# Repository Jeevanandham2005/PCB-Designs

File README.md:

View this project on [CADLAB.io](https://cadlab.io/project/29114). 

# PCB-Designs

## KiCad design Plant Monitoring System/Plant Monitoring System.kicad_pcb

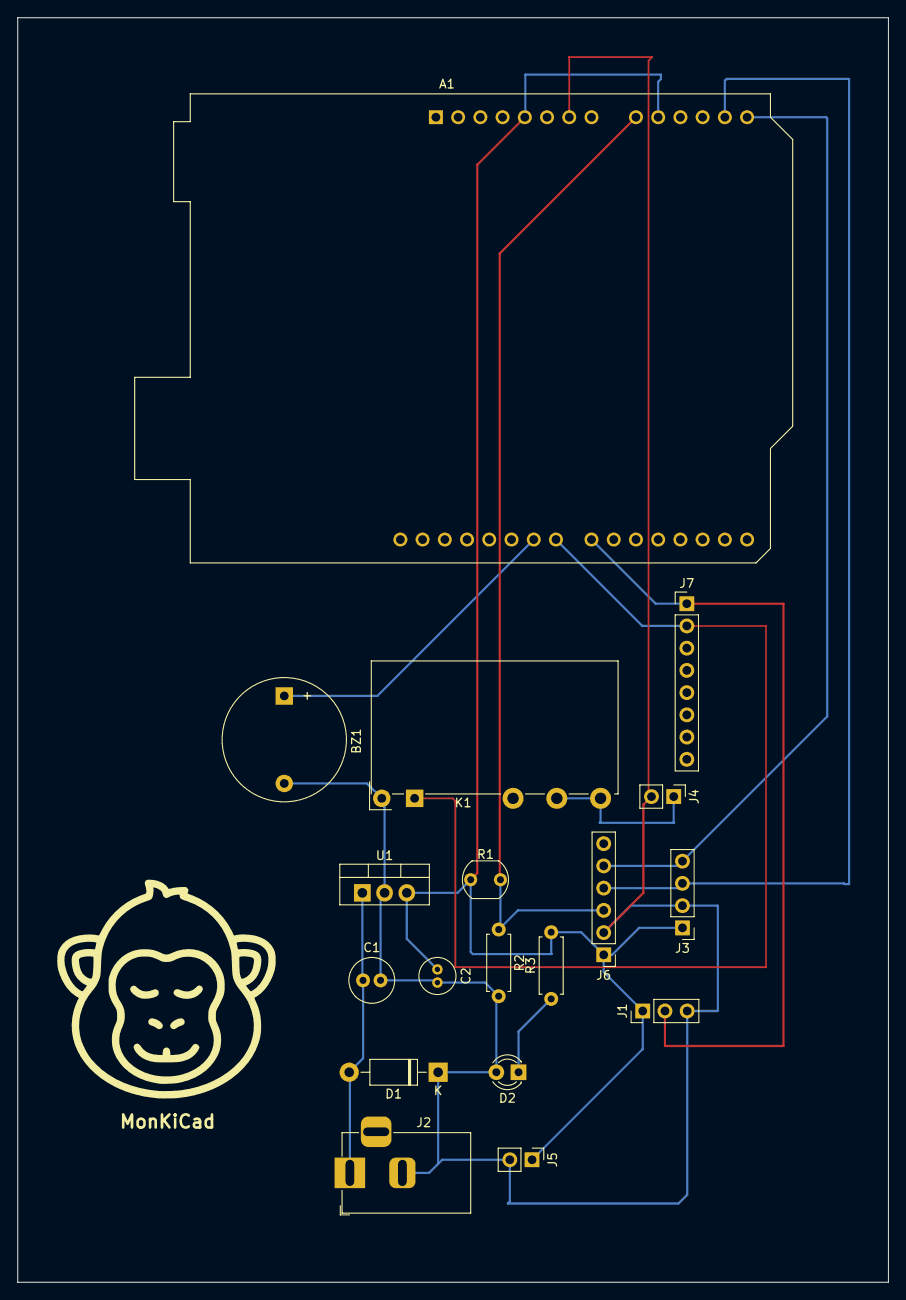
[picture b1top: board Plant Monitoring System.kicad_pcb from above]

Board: 2 copper layers, 99.5 x 144.5 mm, 19 parts (0 on the bottom side), 11 nets.

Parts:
A1: Arduino_UNO_R2
BZ1: Buzzer; Buzzer_D14mm_H7mm_P10mm
C1: 100uF; C_Radial_D5.0mm_H11.0mm_P2.00mm
C2: 10uF; C_Radial_D4.0mm_H5.0mm_P1.50mm
D1: 1N4007; D_DO-41_SOD81_P10.16mm_Horizontal
D2: LED; LED_D3.0mm
J1: DHT11_Connector; PinHeader_1x03_P2.54mm_Vertical
J2: Barrel_Jack; BarrelJack_Horizontal
J3: Soil_Sensor_Connector; PinHeader_1x04_P2.54mm_Vertical
J4, J5: Conn_01x02_Pin; PinHeader_1x02_P2.54mm_Vertical
J6: Conn_01x06_Pin; PinHeader_1x06_P2.54mm_Vertical
J7: Conn_01x08_Pin; PinHeader_1x08_P2.54mm_Vertical
K1: Relay_SPDT; Relay_SPDT_Finder_34.51_Horizontal
Logo: LOGO; monkicadlogo
R1: LDR07; R_LDR_5.1x4.3mm_P3.4mm_Vertical
R2, R3: R; R_Axial_DIN0207_L6.3mm_D2.5mm_P7.62mm_Horizontal
U1: L7805; TO-220-3_Vertical

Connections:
+5V: A1.5 (+5V), A1.10 (A1), C2.1, J1.1, J3.1, J5.1, J6.1, R1.1, R3.2, U1.3 (OUT)
+12V: C1.1, D1.2 (A), J2.1, U1.1 (IN)
/BUZZER_CTRL: A1.24 (D9), BZ1.1 (+)
/DHT11_Out: A1.22 (D7), J1.2, J7.1
/LDR_Out: A1.9 (A0), J6.3, R1.2, R2.1
/LED_OUT: D2.1 (K), R3.1
/PUMP_PWR: J4.1, K1.11, K1.14
/RELAY_CTRL: A1.23 (D8), J7.2, K1.A1
/SCL: A1.14 (SCL/A5), J3.4, J6.5
/SDA: A1.13 (SDA/A4), J3.3, J6.4
GND: A1.7 (GND), BZ1.2 (-), C1.2, C2.2, D1.1 (K), D2.2 (A), J1.3, J2.2, J3.2, J4.2, J5.2, J6.2, K1.A2, R2.2, U1.2 (GND)

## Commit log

2025-03-24 Buck Added
2025-03-24 Boost Added
2025-04-01 Backlink to CADLAB.io has been added.
2025-04-01 Plant Monitoring System Added
